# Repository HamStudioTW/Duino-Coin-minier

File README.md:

```                                                                     
  ╭──╮                        ╭──────────────────╮                  
  |  |                        |  ╭────────────╮  |        ╭──────────╮          
  |  │            ╭──╮        |  |            |  |        |  ╭────╮  ╰───────╮  
  |  ╰────────────╯  |        |  ╰────────────╯  |        |  |    |  ╭────╮  |  
  |  ╭────────────╮  |        |  ╭────────────╮  |        |  |    |  |    |  |  
  |  │            │  |        |  │            │  |        |  |    |  |    |  |  
  |  │            │  |        |  │            │  |        |  |    |  |    |  | 
  ╰──╯            ╰──╯        ╰──╯            ╰──╯        ╰──╯    ╰──╯    ╰──╯  Studio
```

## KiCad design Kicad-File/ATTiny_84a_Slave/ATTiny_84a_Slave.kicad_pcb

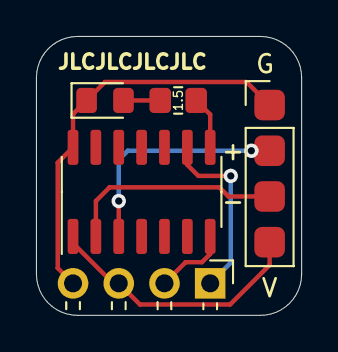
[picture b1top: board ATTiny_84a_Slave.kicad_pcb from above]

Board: 2 copper layers, 14.7 x 15.5 mm, 5 parts (0 on the bottom side), 8 nets.

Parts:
D1: LED; LED_0805_2012Metric_Pad1.15x1.40mm_HandSolder
J1: Conn_To_PCB; PinHeader_1x04_P2.54mm_Horizontal
J2: Conn_USB; PinHeader_1x04_P2.54mm_Vertical
R1: 1.5K; R_0805_2012Metric_Pad1.20x1.40mm_HandSolder
U1: ATtiny84A-SSU; SOIC-14_3.9x8.7mm_P1.27mm

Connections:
D+: J2.2, U1.3
D-: J2.3, U1.2
GND: D1.1, J1.4, J2.1, U1.14
unnamed: D1.2, R1.1
unnamed: R1.2, U1.8
SCL: J1.1, U1.9
SDA: J1.2, U1.7
VCC: J1.3, J2.4, U1.1

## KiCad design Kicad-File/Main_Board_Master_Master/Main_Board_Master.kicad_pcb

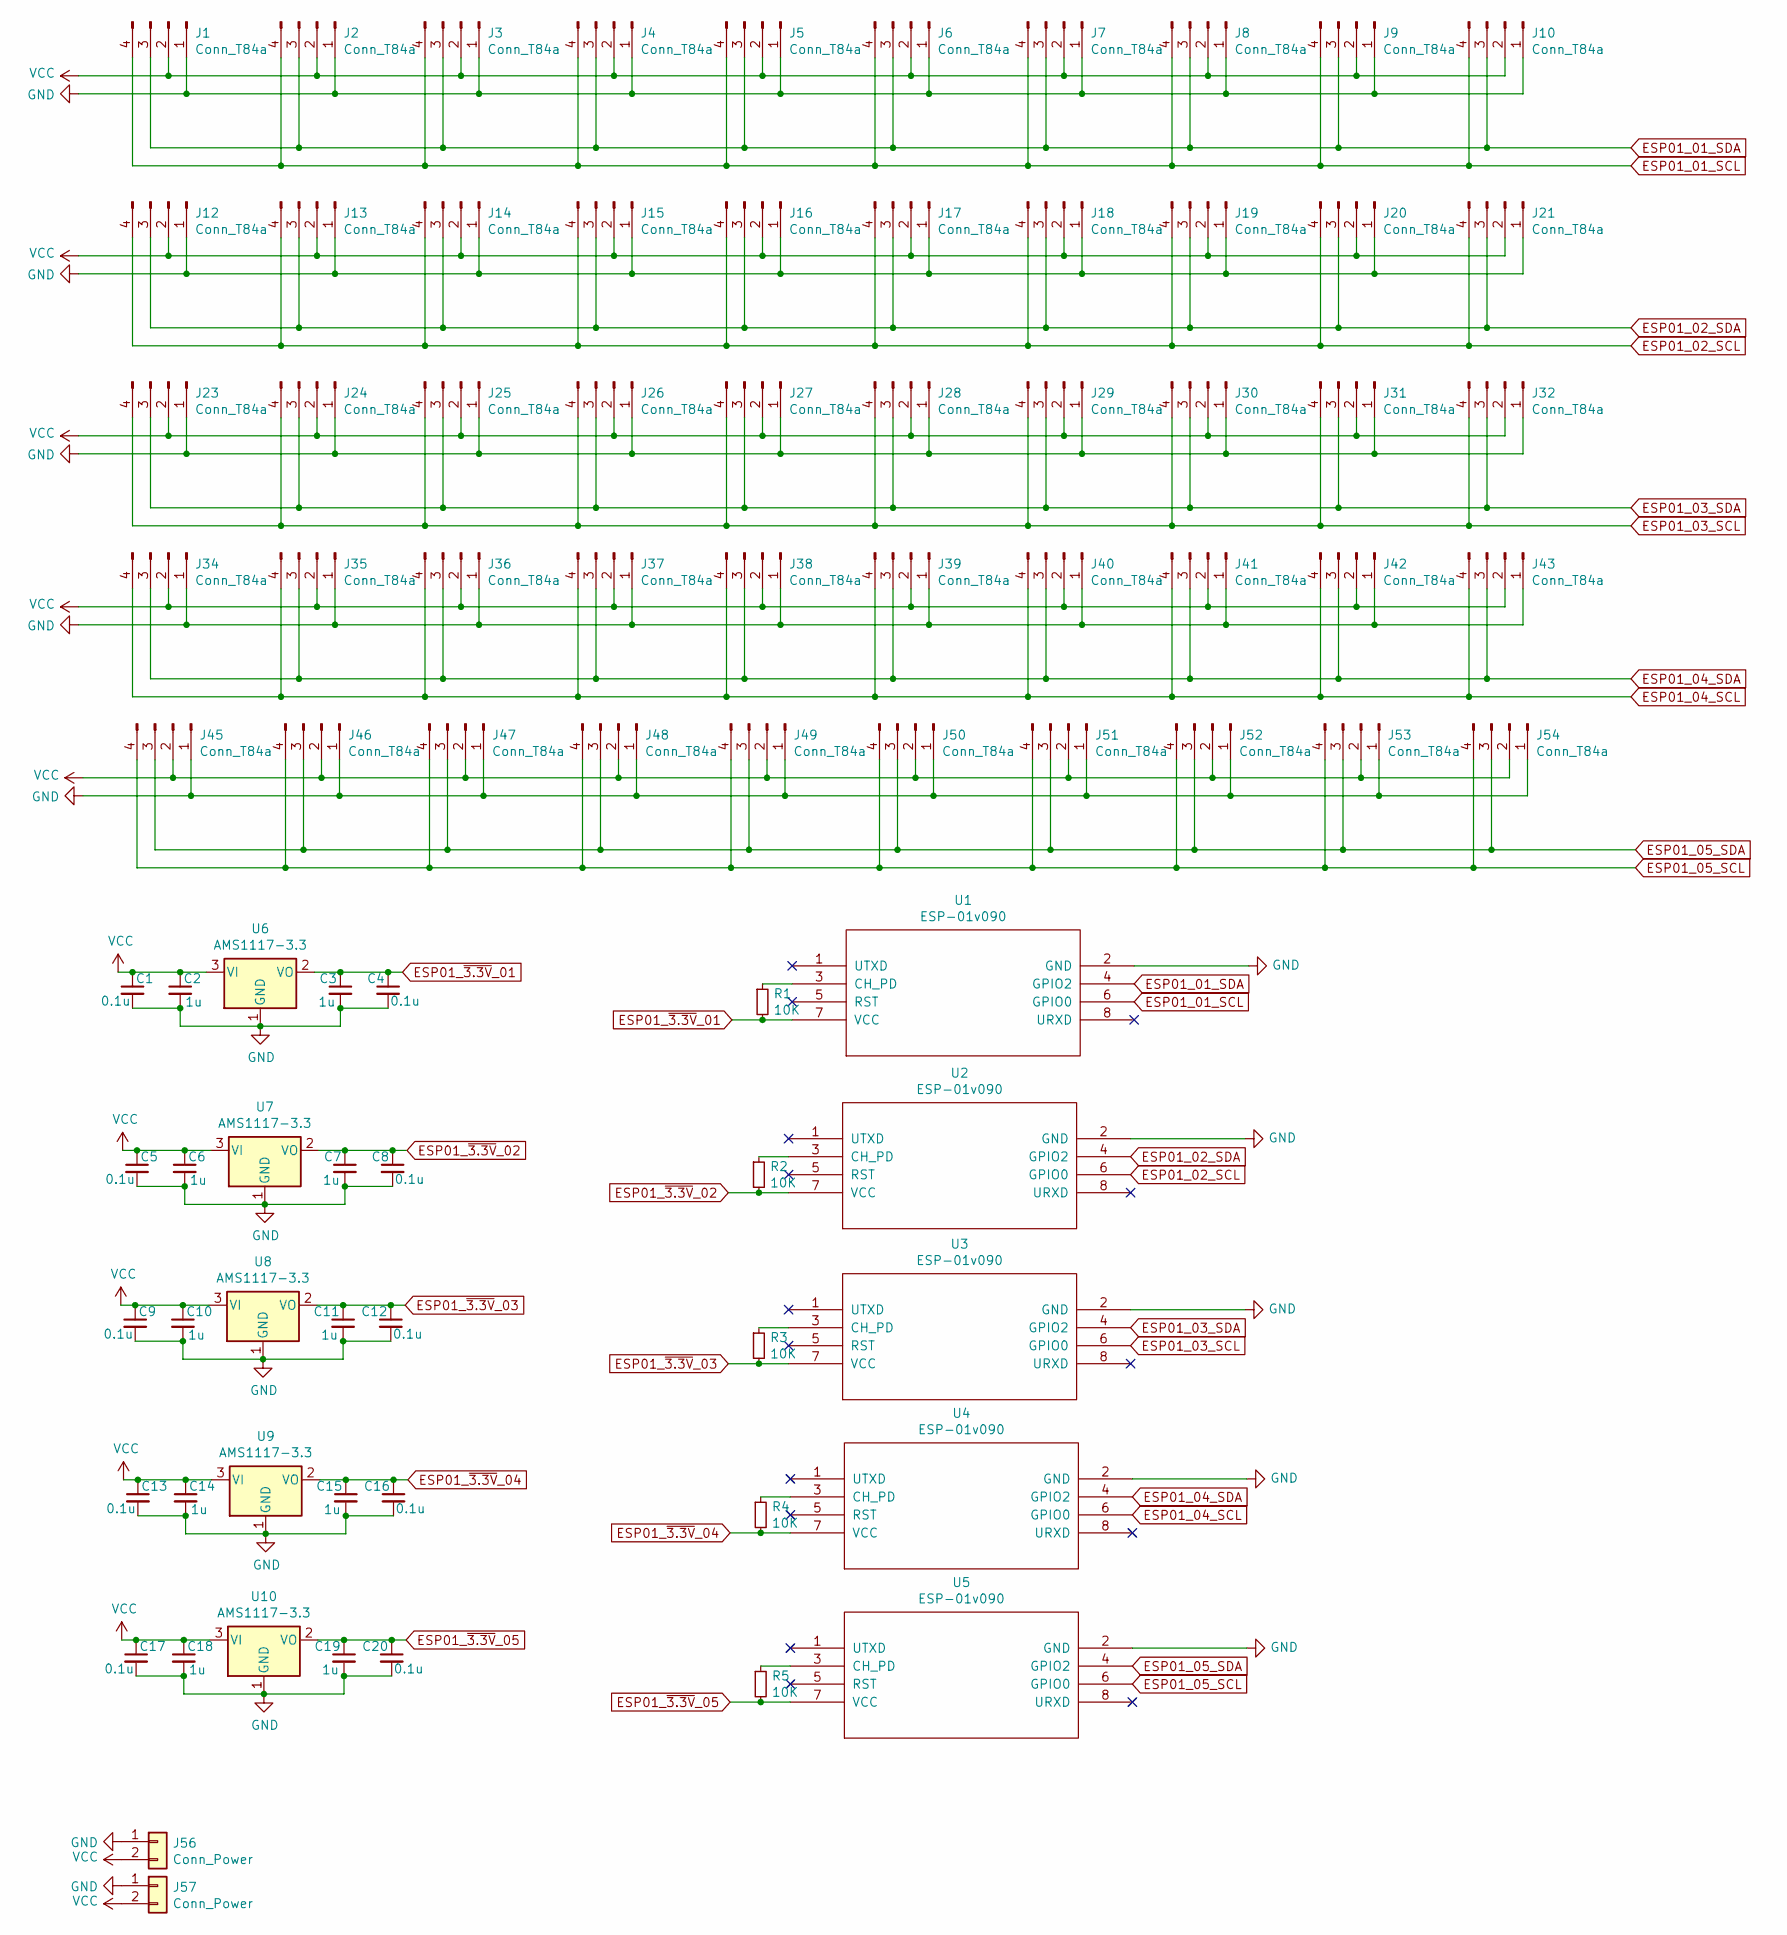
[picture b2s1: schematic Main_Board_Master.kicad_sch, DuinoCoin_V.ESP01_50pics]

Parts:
C1, C4, C5, C8, C9, C12, C13, C16, C17, C20: 0.1u; C_0805_2012Metric_Pad1.18x1.45mm_HandSolder
C2, C3, C6, C7, C10, C11, C14, C15, C18, C19: 1u; C_0805_2012Metric_Pad1.18x1.45mm_HandSolder
J1, J2, J3, J4, J5, J6, J7, J8, J9, J10, J12, J13, J14, J15, J16, J17, J18, J19, J20, J21, J23, J24, J25, J26, J27, J28, J29, J30, J31, J32, J34, J35, J36, J37, J38, J39, J40, J41, J42, J43, J45, J46, J47, J48, J49, J50, J51, J52, J53, J54: Conn_T84a; PinSocket_1x04_P2.54mm_Vertical
J56, J57: Conn_Power; TerminalBlock_bornier-2_P5.08mm
R1, R2, R3, R4, R5: 10K; R_0805_2012Metric_Pad1.20x1.40mm_HandSolder
U1, U2, U3, U4, U5: ESP-01v090; ESP-01
U6, U7, U8, U9, U10: AMS1117-3.3; SOT-223-3_TabPin2

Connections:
ESP01_01_SCL: J1.4, J2.4, J3.4, J4.4, J5.4, J6.4, J7.4, J8.4, J9.4, J10.4, U1.6 (GPIO0)
ESP01_01_SDA: J1.3, J2.3, J3.3, J4.3, J5.3, J6.3, J7.3, J8.3, J9.3, J10.3, U1.4 (GPIO2)
ESP01_02_SCL: J12.4, J13.4, J14.4, J15.4, J16.4, J17.4, J18.4, J19.4, J20.4, J21.4, U2.6 (GPIO0)
ESP01_02_SDA: J12.3, J13.3, J14.3, J15.3, J16.3, J17.3, J18.3, J19.3, J20.3, J21.3, U2.4 (GPIO2)
ESP01_03_SCL: J23.4, J24.4, J25.4, J26.4, J27.4, J28.4, J29.4, J30.4, J31.4, J32.4, U3.6 (GPIO0)
ESP01_03_SDA: J23.3, J24.3, J25.3, J26.3, J27.3, J28.3, J29.3, J30.3, J31.3, J32.3, U3.4 (GPIO2)
ESP01_04_SCL: J34.4, J35.4, J36.4, J37.4, J38.4, J39.4, J40.4, J41.4, J42.4, J43.4, U4.6 (GPIO0)
ESP01_04_SDA: J34.3, J35.3, J36.3, J37.3, J38.3, J39.3, J40.3, J41.3, J42.3, J43.3, U4.4 (GPIO2)
ESP01_05_SCL: J45.4, J46.4, J47.4, J48.4, J49.4, J50.4, J51.4, J52.4, J53.4, J54.4, U5.6 (GPIO0)
ESP01_05_SDA: J45.3, J46.3, J47.3, J48.3, J49.3, J50.3, J51.3, J52.3, J53.3, J54.3, U5.4 (GPIO2)
ESP01_~3.3V_01: C3.1, C4.1, R1.2, U1.7 (VCC), U6.2 (VO)
ESP01_~3.3V_02: C7.1, C8.1, R2.2, U2.7 (VCC), U7.2 (VO)
ESP01_~3.3V_03: C11.1, C12.1, R3.2, U3.7 (VCC), U8.2 (VO)
ESP01_~3.3V_04: C15.1, C16.1, R4.2, U4.7 (VCC), U9.2 (VO)
ESP01_~3.3V_05: C19.1, C20.1, R5.2, U5.7 (VCC), U10.2 (VO)
GND: C1.2, C2.2, C3.2, C4.2, C5.2, C6.2, C7.2, C8.2, C9.2, C10.2, C11.2, C12.2, C13.2, C14.2, C15.2, C16.2, C17.2, C18.2, C19.2, C20.2, J1.1, J2.1, J3.1, J4.1, J5.1, J6.1, J7.1, J8.1, J9.1, J10.1, J12.1, J13.1, J14.1, J15.1, J16.1, J17.1, J18.1, J19.1, J20.1, J21.1, J23.1, J24.1, J25.1, J26.1, J27.1, J28.1, J29.1, J30.1, J31.1, J32.1, J34.1, J35.1, J36.1, J37.1, J38.1, J39.1, J40.1, J41.1, J42.1, J43.1, J45.1, J46.1, J47.1, J48.1, J49.1, J50.1, J51.1, J52.1, J53.1, J54.1, J56.1, J57.1, U1.2 (GND), U2.2 (GND), U3.2 (GND), U4.2 (GND), U5.2 (GND), U6.1 (GND), U7.1 (GND), U8.1 (GND), U9.1 (GND), U10.1 (GND)
unnamed: R1.1, U1.3 (CH_PD)
unnamed: R2.1, U2.3 (CH_PD)
unnamed: R3.1, U3.3 (CH_PD)
unnamed: R4.1, U4.3 (CH_PD)
unnamed: R5.1, U5.3 (CH_PD)
VCC: C1.1, C2.1, C5.1, C6.1, C9.1, C10.1, C13.1, C14.1, C17.1, C18.1, J1.2, J2.2, J3.2, J4.2, J5.2, J6.2, J7.2, J8.2, J9.2, J10.2, J12.2, J13.2, J14.2, J15.2, J16.2, J17.2, J18.2, J19.2, J20.2, J21.2, J23.2, J24.2, J25.2, J26.2, J27.2, J28.2, J29.2, J30.2, J31.2, J32.2, J34.2, J35.2, J36.2, J37.2, J38.2, J39.2, J40.2, J41.2, J42.2, J43.2, J45.2, J46.2, J47.2, J48.2, J49.2, J50.2, J51.2, J52.2, J53.2, J54.2, J56.2, J57.2, U6.3 (VI), U7.3 (VI), U8.3 (VI), U9.3 (VI), U10.3 (VI)

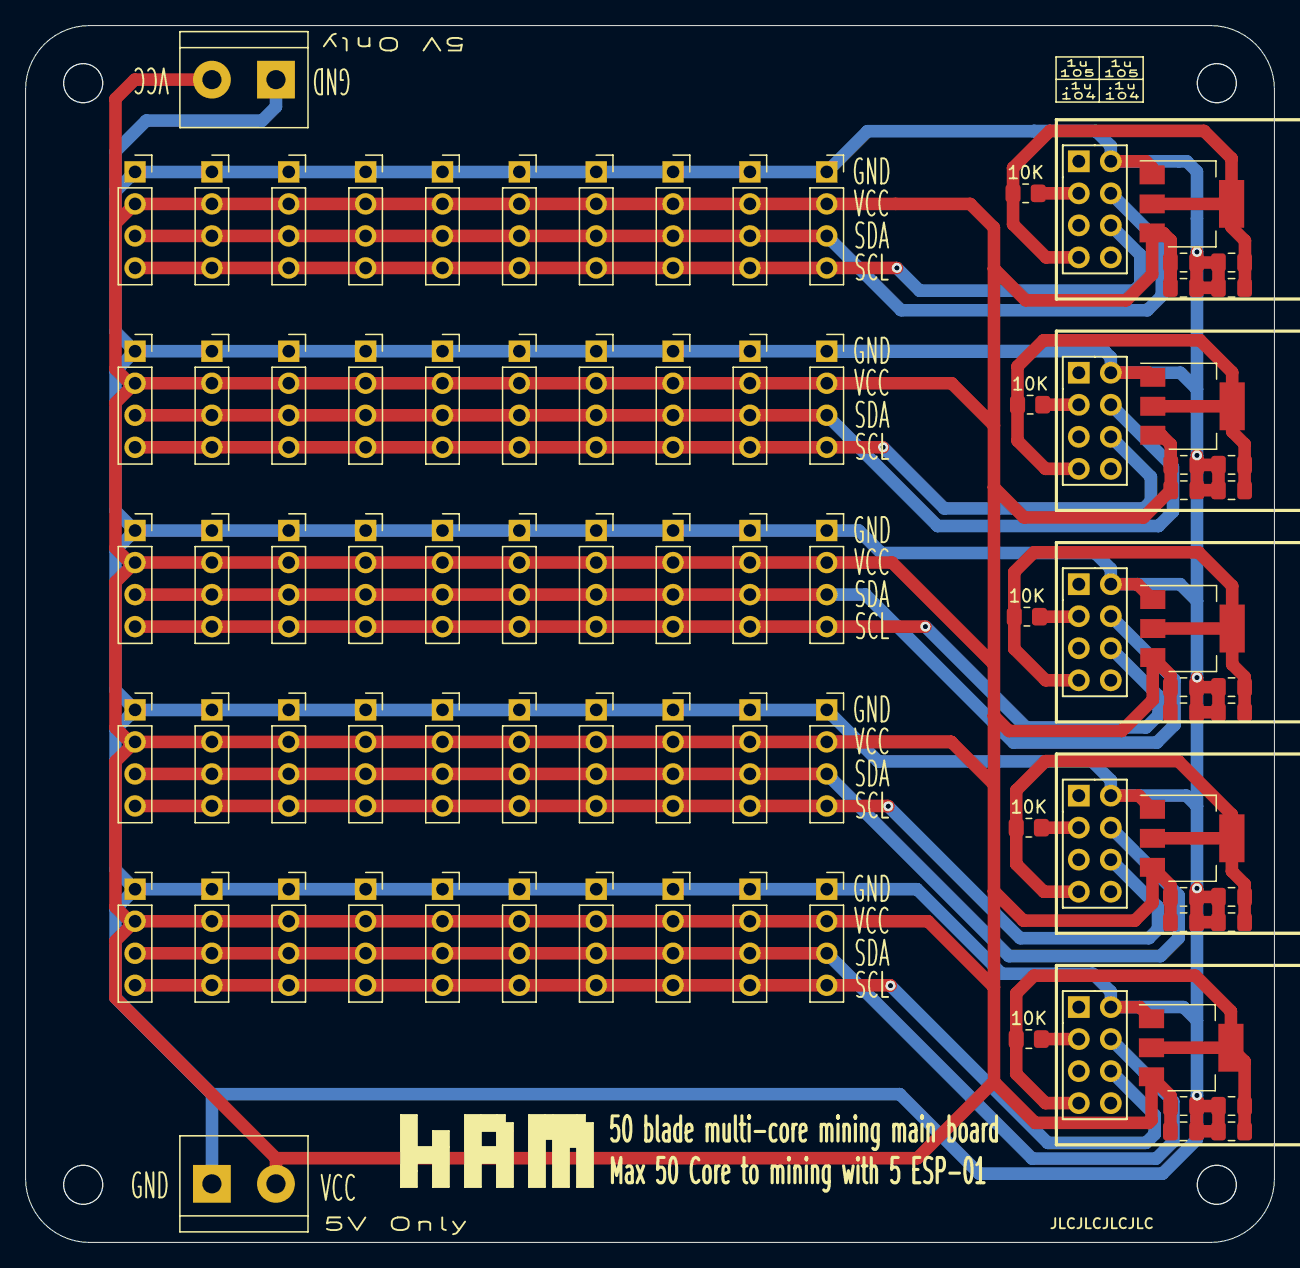
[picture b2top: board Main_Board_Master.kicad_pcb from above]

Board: 2 copper layers, 99.1 x 96.5 mm, 87 parts (0 on the bottom side), 22 nets.

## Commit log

2022-04-03 Add files via upload
    First Upload of this projest
2022-04-03 Add files via upload
    Reupload To make File more easy to access
2022-04-03 ATTiny84a Balde
